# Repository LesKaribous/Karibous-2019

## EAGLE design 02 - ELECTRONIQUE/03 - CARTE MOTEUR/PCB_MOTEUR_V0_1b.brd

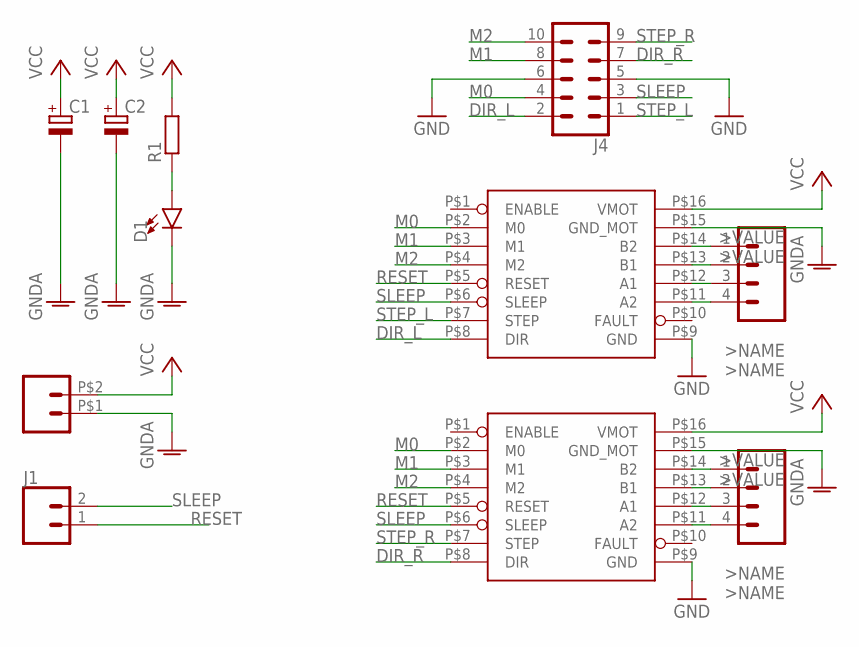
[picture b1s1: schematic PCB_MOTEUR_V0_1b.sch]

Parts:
C1, C2: CPOL-EUE3.5-8; E3,5-8
D1: LED3MM; LED_3MM
J1: CONN_02; 1X02
J2: CONN_027A-C; NSK396-2C
J3, J5: CONN_04POLAR; MOLEX-1X4
J4: CONN_05X2SHD; 2X5-SHROUDED
R1: R-EU_0207/2V; 0207/2V
U$1, U$2: DRV8825; DRIVER_CARRIER_POLOLU_16

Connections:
DIR_L: J4.2, U$1.P$8 (DIR)
DIR_R: J4.7, U$2.P$8 (DIR)
GND: J4.5, J4.6, U$1.P$9 (GND), U$2.P$9 (GND)
GNDA: C1.-, C2.-, D1.K (C), J2.P$1 (1), U$1.P$15 (GND_MOT), U$2.P$15 (GND_MOT)
M0: J4.4, U$1.P$2 (M0), U$2.P$2 (M0)
M1: J4.8, U$1.P$3 (M1), U$2.P$3 (M1)
M2: J4.10, U$1.P$4 (M2), U$2.P$4 (M2)
unnamed: J3.1, U$1.P$14 (B2)
unnamed: J3.2, U$1.P$13 (B1)
unnamed: J3.3, U$1.P$12 (A1)
unnamed: J3.4, U$1.P$11 (A2)
unnamed: D1.A, R1.1
unnamed: J5.1, U$2.P$14 (B2)
unnamed: J5.2, U$2.P$13 (B1)
unnamed: J5.3, U$2.P$12 (A1)
unnamed: J5.4, U$2.P$11 (A2)
RESET: J1.1, U$1.P$5 (RESET), U$2.P$5 (RESET)
SLEEP: J1.2, J4.3, U$1.P$6 (SLEEP), U$2.P$6 (SLEEP)
STEP_L: J4.1, U$1.P$7 (STEP)
STEP_R: J4.9, U$2.P$7 (STEP)
VCC: C1.+, C2.+, J2.P$2 (2), R1.2, U$1.P$16 (VMOT), U$2.P$16 (VMOT)

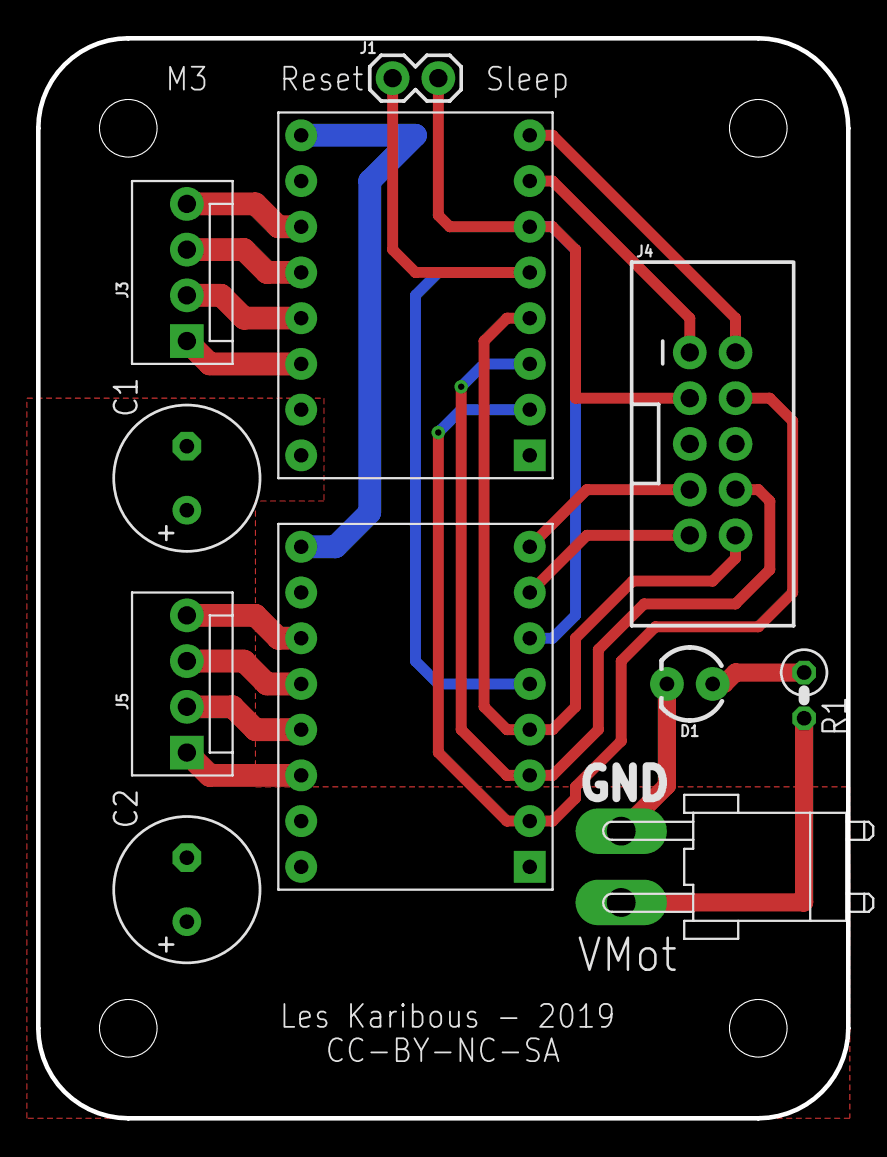
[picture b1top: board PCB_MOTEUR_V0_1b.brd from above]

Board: 2 copper layers, 45.0 x 60.0 mm, 11 parts (0 on the bottom side), 21 nets.

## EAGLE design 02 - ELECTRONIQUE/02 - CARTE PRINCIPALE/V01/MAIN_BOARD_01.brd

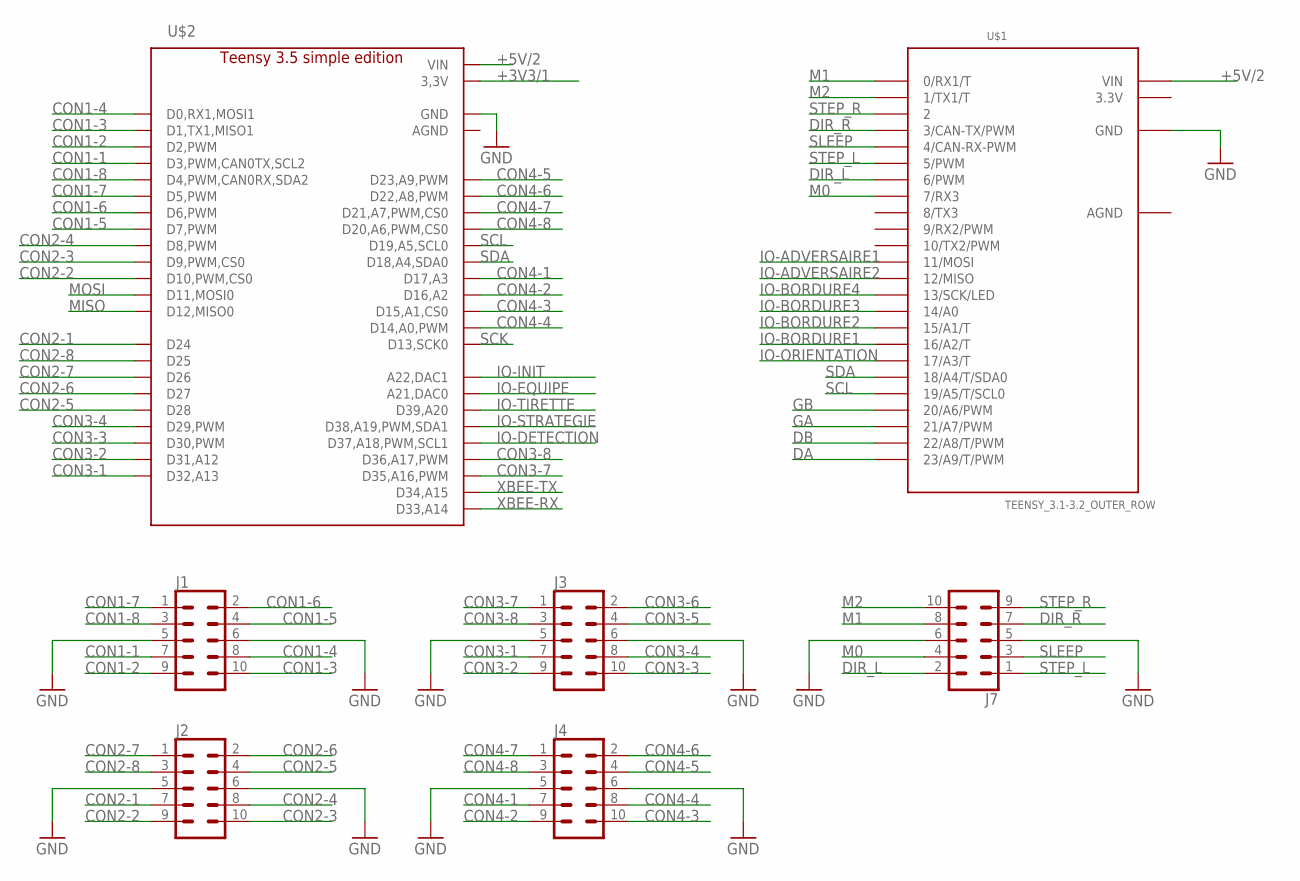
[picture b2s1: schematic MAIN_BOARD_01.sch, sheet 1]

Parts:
J1, J2, J3, J4, J7: CONN_05X2SHD; 2X5-SHROUDED
U$1: TEENSY_3.1-3.2_OUTER_ROW; TEENSY_3.0-3.2&LC_OUTER_ROW
U$2: TEENSY_3.5; TEENSY_3.5_LIGHT

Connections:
3.3V: U$1.3.3V
+3V3/1: U$2.P$15 (3,3V), U$2.P$46 (3,3V); also elsewhere on the board
+5V/2: U$1.V_IN (VIN), U$2.P$48 (VIN); also elsewhere on the board
AGND: U$1.AGND
CON1-1: J1.7, U$2.P$5 (D3,PWM,CAN0TX,SCL2)
CON1-2: J1.9, U$2.P$4 (D2,PWM)
CON1-3: J1.10, U$2.P$3 (D1,TX1,MISO1)
CON1-4: J1.8, U$2.P$2 (D0,RX1,MOSI1)
CON1-5: J1.4, U$2.P$9 (D7,PWM)
CON1-6: J1.2, U$2.P$8 (D6,PWM)
CON1-7: J1.1, U$2.P$7 (D5,PWM)
CON1-8: J1.3, U$2.P$6 (D4,PWM,CAN0RX,SDA2)
CON2-1: J2.7, U$2.P$16 (D24)
CON2-2: J2.9, U$2.P$12 (D10,PWM,CS0)
CON2-3: J2.10, U$2.P$11 (D9,PWM,CS0)
CON2-4: J2.8, U$2.P$10 (D8,PWM)
CON2-5: J2.4, U$2.P$20 (D28)
CON2-6: J2.2, U$2.P$19 (D27)
CON2-7: J2.1, U$2.P$18 (D26)
CON2-8: J2.3, U$2.P$17 (D25)
CON3-1: J3.7, U$2.P$24 (D32,A13)
CON3-2: J3.9, U$2.P$23 (D31,A12)
CON3-3: J3.10, U$2.P$22 (D30,PWM)
CON3-4: J3.8, U$2.P$21 (D29,PWM)
CON3-5: J3.4
CON3-6: J3.2
CON3-7: J3.1, U$2.P$27 (D35,A16,PWM)
CON3-8: J3.3, U$2.P$28 (D36,A17,PWM)
CON4-1: J4.7, U$2.P$39 (D17,A3)
CON4-2: J4.9, U$2.P$38 (D16,A2)
CON4-3: J4.10, U$2.P$37 (D15,A1,CS0)
CON4-4: J4.8, U$2.P$36 (D14,A0,PWM)
CON4-5: J4.4, U$2.P$45 (D23,A9,PWM)
CON4-6: J4.2, U$2.P$44 (D22,A8,PWM)
CON4-7: J4.1, U$2.P$43 (D21,A7,PWM,CS0)
CON4-8: J4.3, U$2.P$42 (D20,A6,PWM,CS0)
DA: U$1.23/A9 (23/A9/T/PWM); also elsewhere on the board
DB: U$1.22/A8 (22/A8/T/PWM); also elsewhere on the board
DIR_L: J7.2, U$1.6 (6/PWM)
DIR_R: J7.7, U$1.3 (3/CAN-TX/PWM)
GA: U$1.21/A7 (21/A7/PWM); also elsewhere on the board
GB: U$1.20/A6 (20/A6/PWM); also elsewhere on the board
GND: J1.5, J1.6, J2.5, J2.6, J3.5, J3.6, J4.5, J4.6, J7.5, J7.6, U$1.GND, U$2.GND, U$2.P$34 (GND); also elsewhere on the board
IO-ADVERSAIRE1: U$1.11 (11/MOSI); also elsewhere on the board
IO-ADVERSAIRE2: U$1.12 (12/MISO); also elsewhere on the board
IO-BORDURE1: U$1.16/A2 (16/A2/T); also elsewhere on the board
IO-BORDURE2: U$1.15/A1 (15/A1/T); also elsewhere on the board
IO-BORDURE3: U$1.14/A0; also elsewhere on the board
IO-BORDURE4: U$1.13 (13/SCK/LED); also elsewhere on the board
IO-DETECTION: U$2.P$29 (D37,A18,PWM,SCL1); also elsewhere on the board
IO-EQUIPE: U$2.P$32 (A21,DAC0); also elsewhere on the board
IO-INIT: U$2.P$33 (A22,DAC1); also elsewhere on the board
IO-ORIENTATION: U$1.17/A3 (17/A3/T); also elsewhere on the board
IO-STRATEGIE: U$2.P$30 (D38,A19,PWM,SDA1); also elsewhere on the board
IO-TIRETTE: U$2.P$31 (D39,A20); also elsewhere on the board
M0: J7.4, U$1.7 (7/RX3)
M1: J7.8, U$1.0 (0/RX1/T)
M2: J7.10, U$1.1 (1/TX1/T)
MISO: U$2.P$14 (D12,MISO0); also elsewhere on the board
MOSI: U$2.P$13 (D11,MOSI0); also elsewhere on the board
SCK: U$2.P$35 (D13,SCK0); also elsewhere on the board
SCL: U$1.19/A5 (19/A5/T/SCL0), U$2.P$41 (D19,A5,SCL0); also elsewhere on the board
SDA: U$1.18/A4 (18/A4/T/SDA0), U$2.P$40 (D18,A4,SDA0); also elsewhere on the board
SLEEP: J7.3, U$1.4 (4/CAN-RX-PWM)
STEP_L: J7.1, U$1.5 (5/PWM)
STEP_R: J7.9, U$1.2
XBEE-RX: U$2.P$25 (D33,A14); also elsewhere on the board
XBEE-TX: U$2.P$26 (D34,A15); also elsewhere on the board

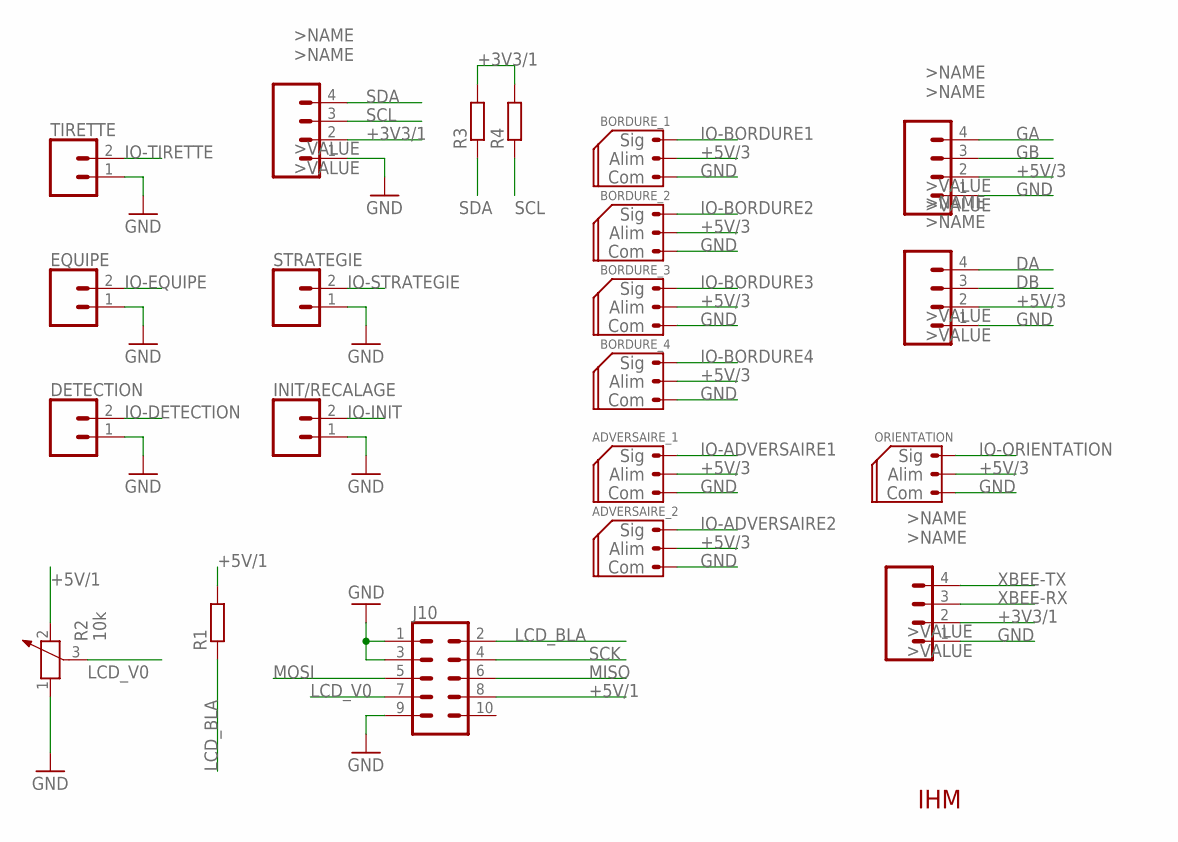
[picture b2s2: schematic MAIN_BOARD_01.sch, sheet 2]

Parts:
ADVERSAIRE_1, ADVERSAIRE_2: CONN_03_SERVO; MOLEX-1X3
BORDURE_1, BORDURE_2, BORDURE_3, BORDURE_4: CONN_03_SERVO; MOLEX-1X3
COM-I2C: CONN_04POLAR; MOLEX-1X4
COM-XBEE: CONN_04POLAR; MOLEX-1X4
DETECTION: CONN_02POLAR; MOLEX-1X2
ENC_DROIT: CONN_04POLAR; MOLEX-1X4
ENC_GAUCHE: CONN_04POLAR; MOLEX-1X4
EQUIPE: CONN_02POLAR; MOLEX-1X2
INIT/RECALAGE: CONN_02POLAR; MOLEX-1X2
J10: CONN_05X2SHD; 2X5-SHROUDED
ORIENTATION: CONN_03_SERVO; MOLEX-1X3
R1, R3, R4: R-EU_R1206; R1206
R2: 10k; PT-10
STRATEGIE: CONN_02POLAR; MOLEX-1X2
TIRETTE: CONN_02POLAR; MOLEX-1X2

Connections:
+3V3/1: COM-I2C.2, COM-XBEE.2, R3.2, R4.2; also elsewhere on the board
+5V/1: J10.8, R1.2, R2.2; also elsewhere on the board
+5V/3: ADVERSAIRE_1.2, ADVERSAIRE_2.2, BORDURE_1.2, BORDURE_2.2, BORDURE_3.2, BORDURE_4.2, ENC_DROIT.2, ENC_GAUCHE.2, ORIENTATION.2; also elsewhere on the board
DA: ENC_DROIT.4; also elsewhere on the board
DB: ENC_DROIT.3; also elsewhere on the board
GA: ENC_GAUCHE.4; also elsewhere on the board
GB: ENC_GAUCHE.3; also elsewhere on the board
GND: ADVERSAIRE_1.1, ADVERSAIRE_2.1, BORDURE_1.1, BORDURE_2.1, BORDURE_3.1, BORDURE_4.1, COM-I2C.1, COM-XBEE.1, DETECTION.1, ENC_DROIT.1, ENC_GAUCHE.1, EQUIPE.1, INIT/RECALAGE.1, J10.1, J10.3, J10.9, ORIENTATION.1, R2.1, STRATEGIE.1, TIRETTE.1; also elsewhere on the board
IO-ADVERSAIRE1: ADVERSAIRE_1.3; also elsewhere on the board
IO-ADVERSAIRE2: ADVERSAIRE_2.3; also elsewhere on the board
IO-BORDURE1: BORDURE_1.3; also elsewhere on the board
IO-BORDURE2: BORDURE_2.3; also elsewhere on the board
IO-BORDURE3: BORDURE_3.3; also elsewhere on the board
IO-BORDURE4: BORDURE_4.3; also elsewhere on the board
IO-DETECTION: DETECTION.2; also elsewhere on the board
IO-EQUIPE: EQUIPE.2; also elsewhere on the board
IO-INIT: INIT/RECALAGE.2; also elsewhere on the board
IO-ORIENTATION: ORIENTATION.3; also elsewhere on the board
IO-STRATEGIE: STRATEGIE.2; also elsewhere on the board
IO-TIRETTE: TIRETTE.2; also elsewhere on the board
LCD_BLA: J10.2, R1.1
LCD_V0: J10.7, R2.3
MISO: J10.6; also elsewhere on the board
MOSI: J10.5; also elsewhere on the board
SCK: J10.4; also elsewhere on the board
SCL: COM-I2C.3, R4.1; also elsewhere on the board
SDA: COM-I2C.4, R3.1; also elsewhere on the board
XBEE-RX: COM-XBEE.3; also elsewhere on the board
XBEE-TX: COM-XBEE.4; also elsewhere on the board

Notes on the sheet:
IHM

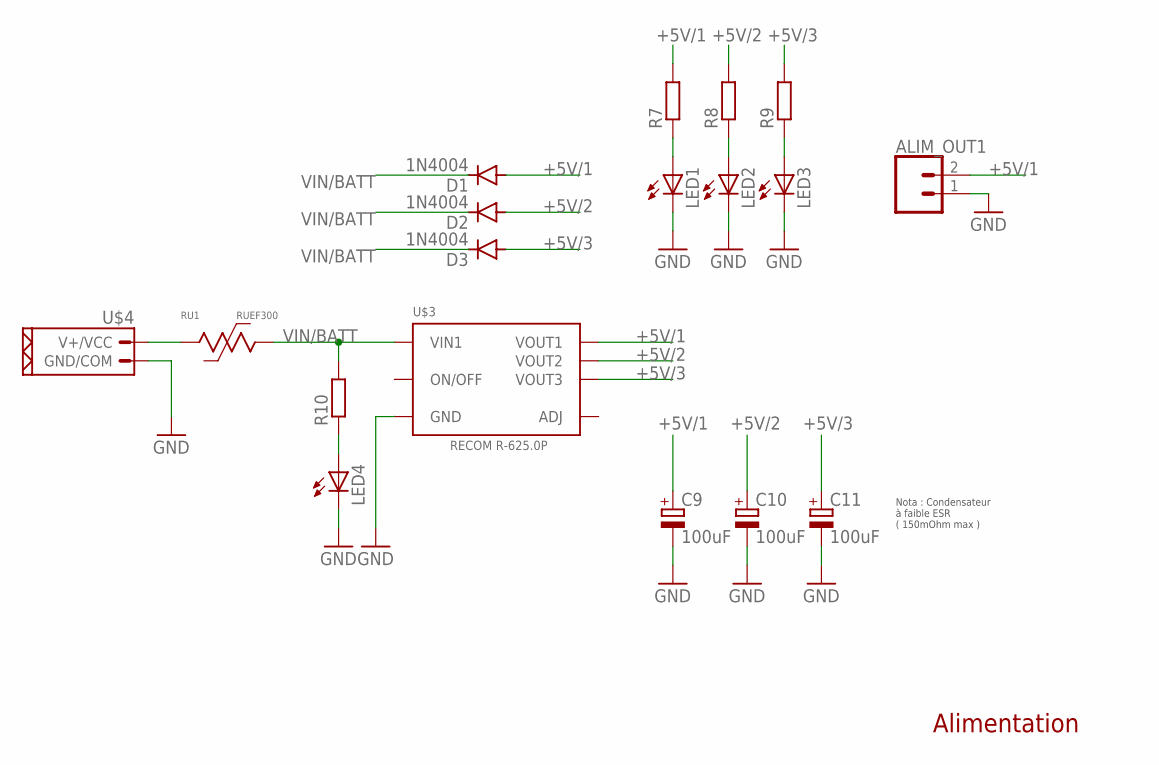
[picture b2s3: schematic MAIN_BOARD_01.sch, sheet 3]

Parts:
ALIM_OUT1: CONN_02POLAR; MOLEX-1X2
C9, C10, C11: 100uF; E5-10,5
D1, D2, D3: 1N4004; DO41-10
LED1, LED2, LED3, LED4: LED_E; LED_1206
R7, R8, R9, R10: R-EU_R1206; R1206
RU1: RUEF300
U$3: R-625.0P; R-6XXXP
U$4: CONN_02_PUI; NSK396-2C

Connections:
+5V/1: ALIM_OUT1.2, C9.+, D1.A, R7.2, U$3.P$9 (VOUT1); also elsewhere on the board
+5V/2: C10.+, D2.A, R8.2, U$3.P$10 (VOUT2); also elsewhere on the board
+5V/3: C11.+, D3.A, R9.2, U$3.P$11 (VOUT3); also elsewhere on the board
ADJ: U$3.P$12 (ADJ)
GND: ALIM_OUT1.1, C9.-, C10.-, C11.-, LED1.C, LED2.C, LED3.C, LED4.C, U$3.P$5 (GND), U$3.P$6 (GND), U$3.P$7 (GND), U$3.P$8 (GND), U$4.P$1 (GND/COM); also elsewhere on the board
unnamed: LED1.A, R7.1
unnamed: LED4.A, R10.1
unnamed: RU1.P$1, U$4.P$2 (V+/VCC)
unnamed: LED2.A, R8.1
unnamed: LED3.A, R9.1
VIN/BATT: D1.C, D2.C, D3.C, R10.2, RU1.P$2, U$3.P$2 (VIN1), U$3.P$3 (VIN1), U$3.P$4 (VIN1)

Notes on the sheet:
Nota : Condensateur à faible ESR ( 150mOhm max )
Alimentation

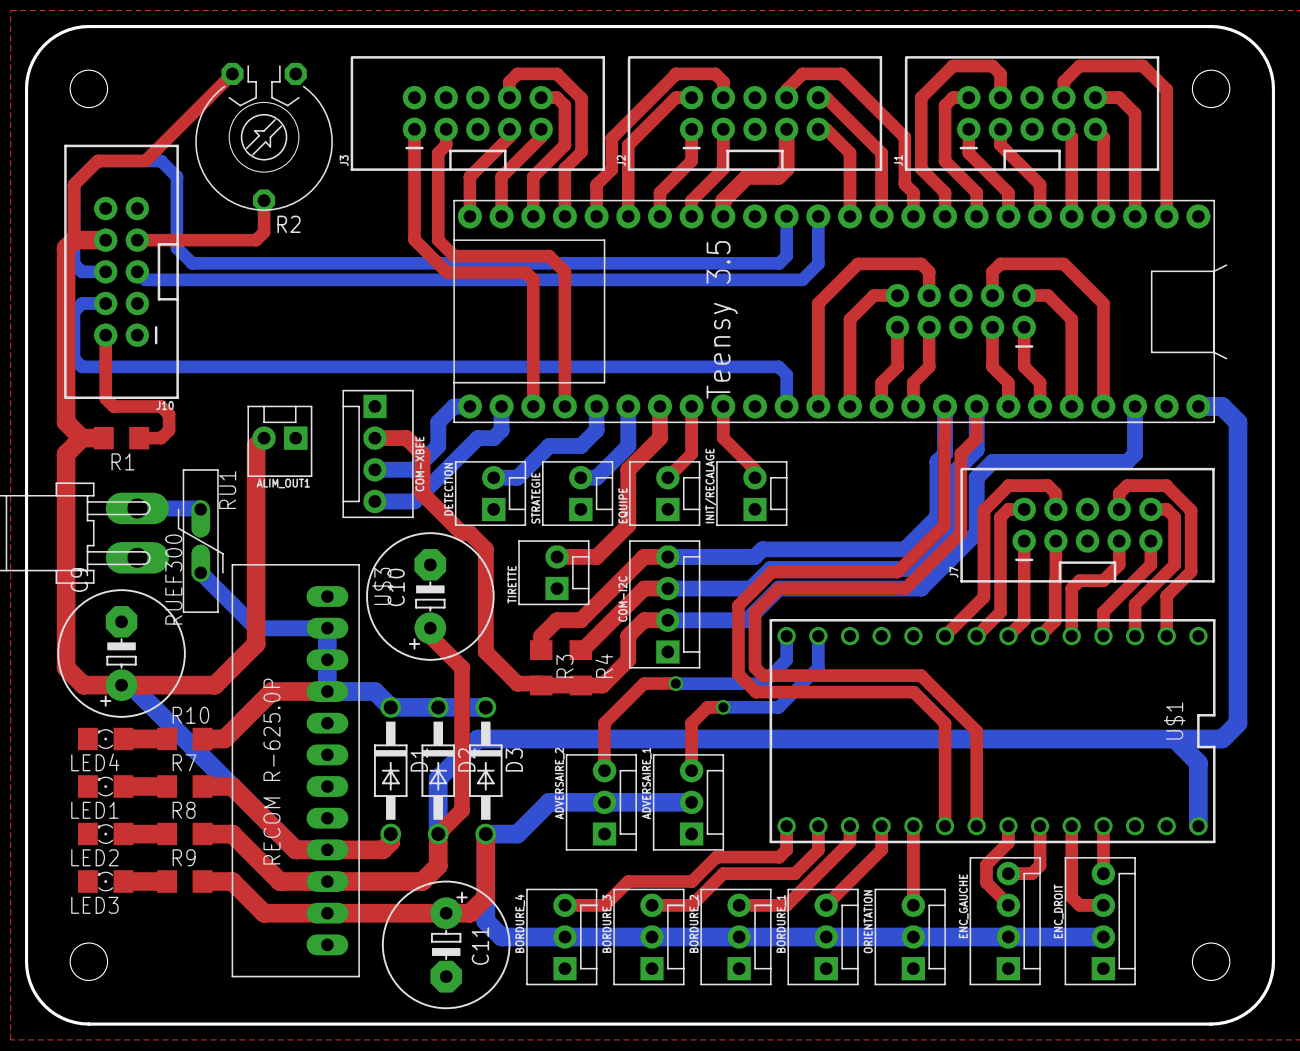
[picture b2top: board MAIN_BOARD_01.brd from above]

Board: 2 copper layers, 100.0 x 80.0 mm, 46 parts (1 on the bottom side), 74 nets.

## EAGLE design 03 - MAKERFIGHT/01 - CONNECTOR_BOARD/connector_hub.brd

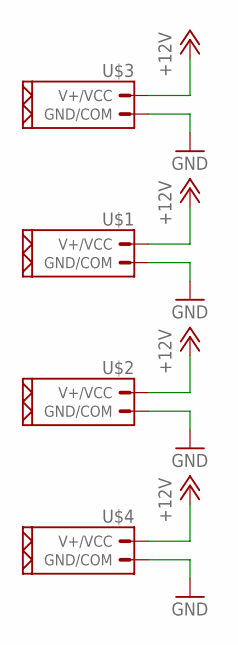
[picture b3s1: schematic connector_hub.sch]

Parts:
U$1, U$2, U$3, U$4: CONN_02_PUIXT60; XT60

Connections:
+12V: U$1.P$1 (V+/VCC), U$2.P$1 (V+/VCC), U$3.P$1 (V+/VCC), U$4.P$1 (V+/VCC)
GND: U$1.P$2 (GND/COM), U$2.P$2 (GND/COM), U$3.P$2 (GND/COM), U$4.P$2 (GND/COM)

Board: 2 copper layers, 4 parts (0 on the bottom side), 2 nets, no tracks yet.

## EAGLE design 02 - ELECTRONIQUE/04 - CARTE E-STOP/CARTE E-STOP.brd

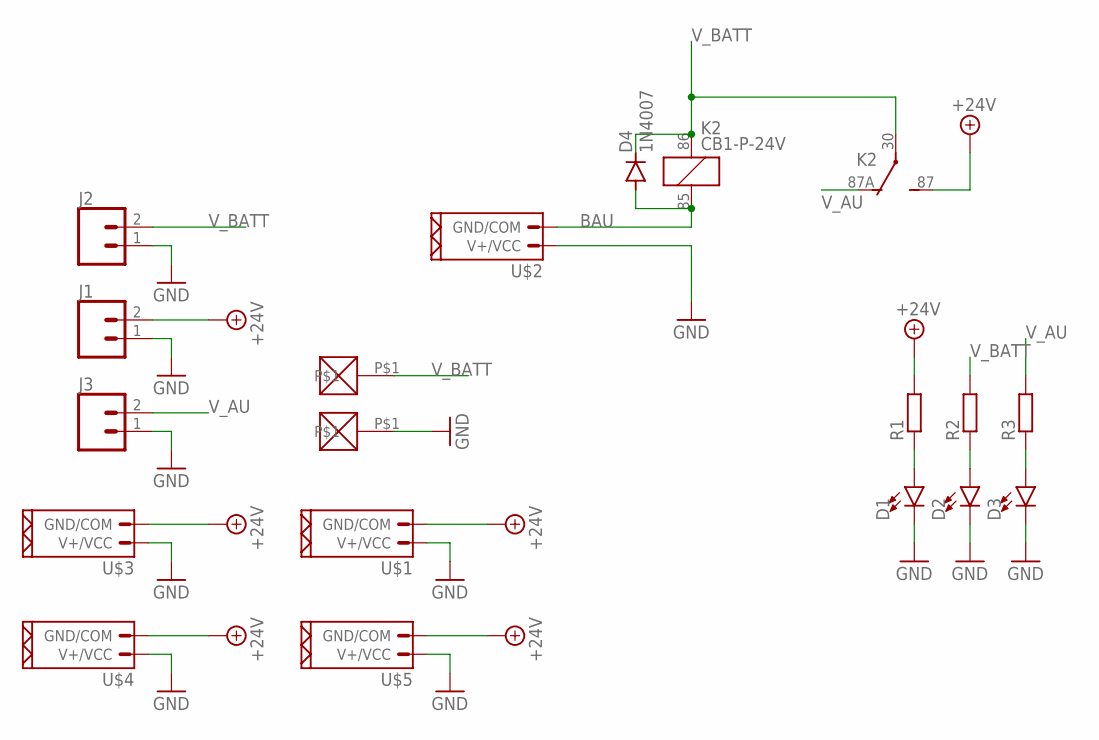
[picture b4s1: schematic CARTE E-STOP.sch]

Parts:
D1, D2, D3: LED3MM; LED_3MM
D4: 1N4007; DO41-10
GND_BATT: BAT_WIRE_SOLD; LARGE_PAD_BATT
J1, J2, J3: CONN_02POLAR; MOLEX-1X2
K2: CB1-P-24V; CB1
R1, R2, R3: R-EU_0207/2V; 0207/2V
U$1, U$2, U$3, U$4, U$5: CONN_02_PUI; NSK396-2C
V+BATT: BAT_WIRE_SOLD; LARGE_PAD_BATT

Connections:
+24V: J1.2, K2.87 (S), R1.2, U$1.P$1 (GND/COM), U$3.P$1 (GND/COM), U$4.P$1 (GND/COM), U$5.P$1 (GND/COM)
BAU: D4.A, K2.85 (2), U$2.P$1 (GND/COM)
GND: D1.K (C), D2.K (C), D3.K (C), GND_BATT.P$1, J1.1, J2.1, J3.1, U$1.P$2 (V+/VCC), U$2.P$2 (V+/VCC), U$3.P$2 (V+/VCC), U$4.P$2 (V+/VCC), U$5.P$2 (V+/VCC)
unnamed: D1.A, R1.1
unnamed: D2.A, R2.1
unnamed: D3.A, R3.1
V_AU: J3.2, K2.87A (O), R3.2
V_BATT: D4.C, J2.2, K2.30, K2.86 (1), R2.2, V+BATT.P$1

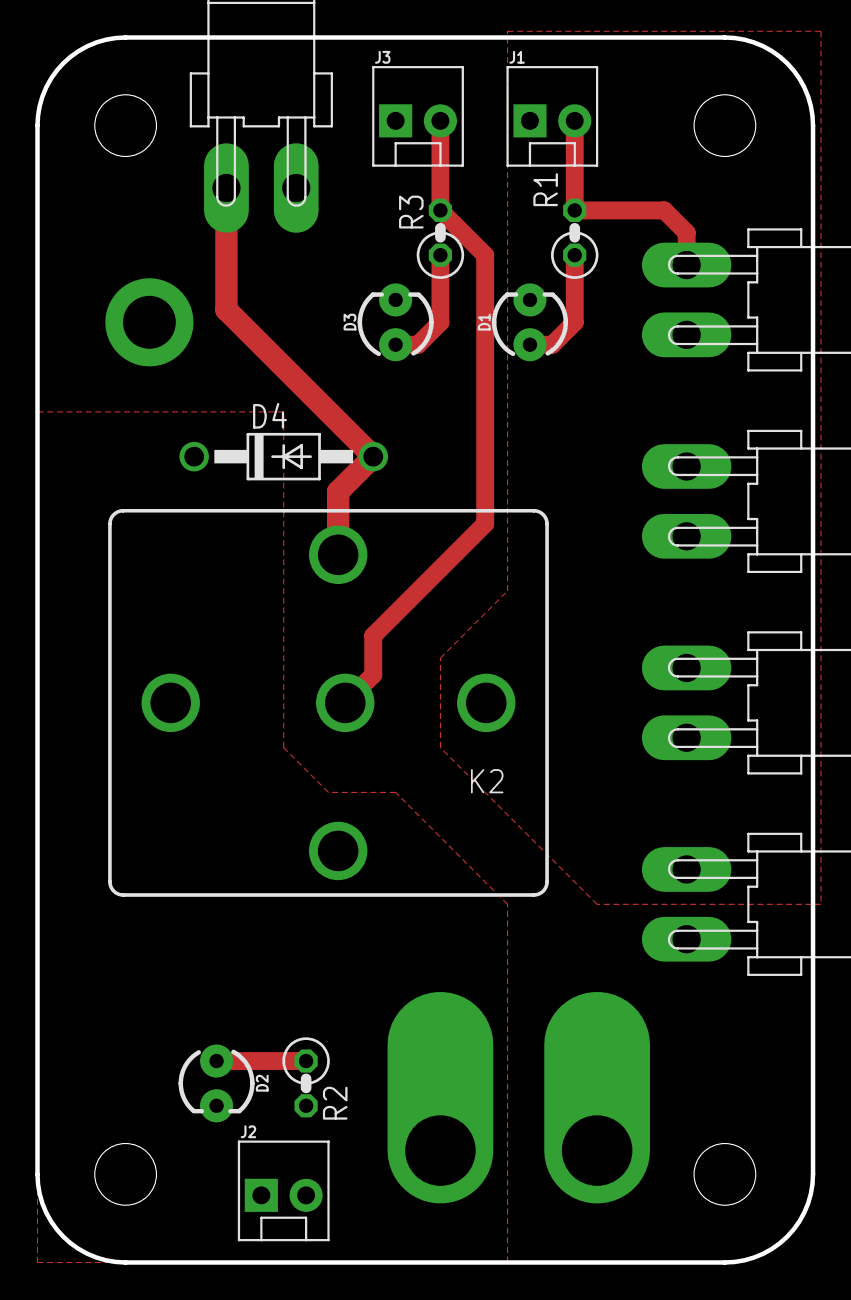
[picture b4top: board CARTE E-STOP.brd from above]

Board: 2 copper layers, 44.0 x 69.5 mm, 18 parts (0 on the bottom side), 8 nets.

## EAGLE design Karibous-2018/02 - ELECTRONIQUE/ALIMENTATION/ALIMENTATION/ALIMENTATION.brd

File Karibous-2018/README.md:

# Karibous-2018
Les Karibous - Coupe de France de robotique 2018

Fichiers de l'electronqiue et de la partie programmation du robot 2018 de l'équipe des Karibous.
Pour la documentation et les fichiers mécaniques, veuillez vous reporter à notre site web : https://sites.google.com/view/leskaribous/la-coupe-de-robotique/robot-2018

### Licence :
L'integralité du contenu est utlisable sous licence CC-BY-NC-SA

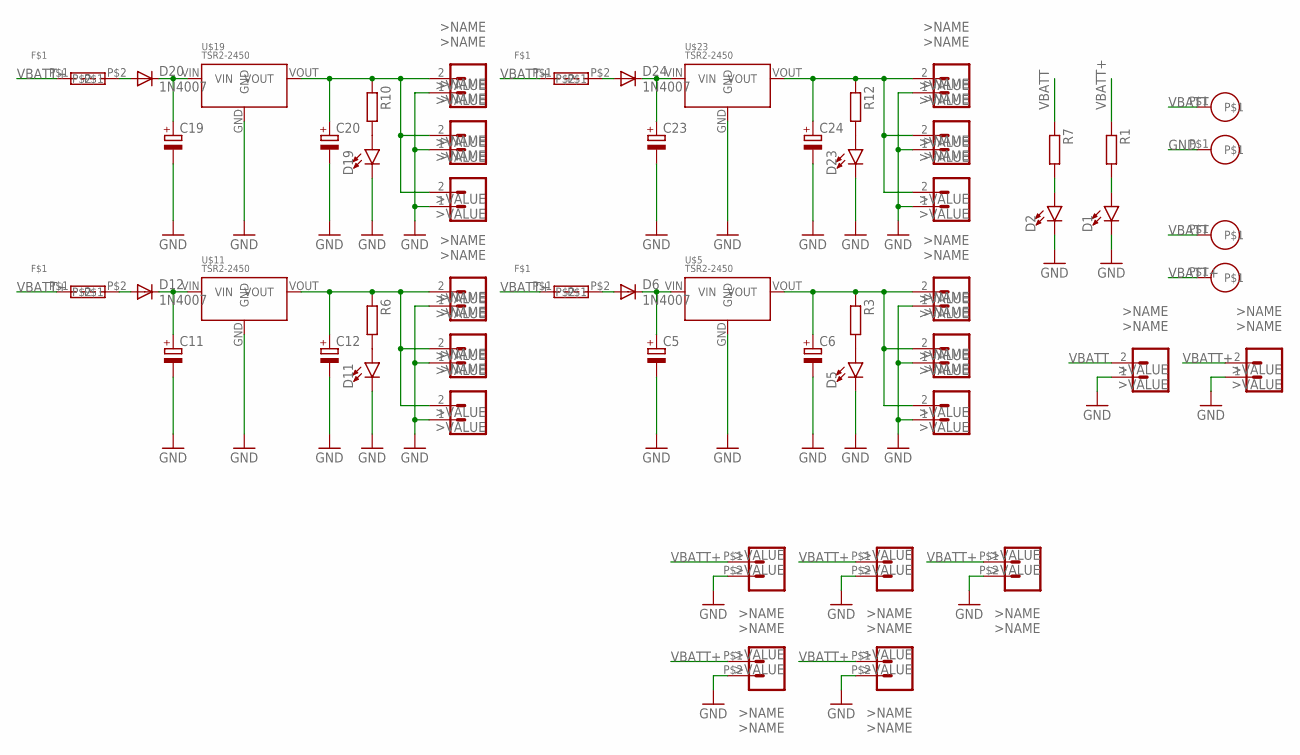
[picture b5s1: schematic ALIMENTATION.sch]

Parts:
C5, C6, C11, C12, C19, C20, C23, C24: CPOL-EUE2-5; E2-5
D1, D2, D5, D11, D19, D23: LED3MM; LED_3MM
D6, D12, D20, D24: 1N4007; DO41-10
J1, J2, J7, J8, J9, J16, J17, J18, J28, J29, J30, J34, J35, J36: CONN_02POLAR; MOLEX-1X2
J3, J10, J11, J12, J13: CONN_027A-C; NSK396-2C
R1, R3, R6, R7, R10, R12: R-EU_0204/2V; 0204V
U$1, U$2, U$13, U$14: BATTERY_PAD
U$5, U$11, U$19, U$23: TSR2-2450
U$6, U$12, U$20, U$24: RUEF_POLY; RUEF185

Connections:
GND: C5.-, C6.-, C11.-, C12.-, C19.-, C20.-, C23.-, C24.-, D1.K (C), D2.K (C), D5.K (C), D11.K (C), D19.K (C), D23.K (C), J1.1, J2.1, J3.P$2 (2), J7.1, J8.1, J9.1, J10.P$2 (2), J11.P$2 (2), J12.P$2 (2), J13.P$2 (2), J16.1, J17.1, J18.1, J28.1, J29.1, J30.1, J34.1, J35.1, J36.1, U$2.P$1, U$5.GND, U$11.GND, U$19.GND, U$23.GND
unnamed: D1.A, R1.2
unnamed: D2.A, R7.2
unnamed: C6.+, J7.2, J8.2, J9.2, R3.1, U$5.VOUT
unnamed: D5.A, R3.2
unnamed: C5.+, D6.C, U$5.VIN
unnamed: D6.A, U$6.P$2
unnamed: C12.+, J16.2, J17.2, J18.2, R6.1, U$11.VOUT
unnamed: D11.A, R6.2
unnamed: C11.+, D12.C, U$11.VIN
unnamed: D12.A, U$12.P$2
unnamed: C20.+, J28.2, J29.2, J30.2, R10.1, U$19.VOUT
unnamed: D19.A, R10.2
unnamed: C19.+, D20.C, U$19.VIN
unnamed: D20.A, U$20.P$2
unnamed: C24.+, J34.2, J35.2, J36.2, R12.1, U$23.VOUT
unnamed: D23.A, R12.2
unnamed: C23.+, D24.C, U$23.VIN
unnamed: D24.A, U$24.P$2
VBATT: J1.2, R7.1, U$1.P$1, U$13.P$1
VBATT+: J2.2, J3.P$1 (1), J10.P$1 (1), J11.P$1 (1), J12.P$1 (1), J13.P$1 (1), R1.1, U$6.P$1, U$12.P$1, U$14.P$1, U$20.P$1, U$24.P$1

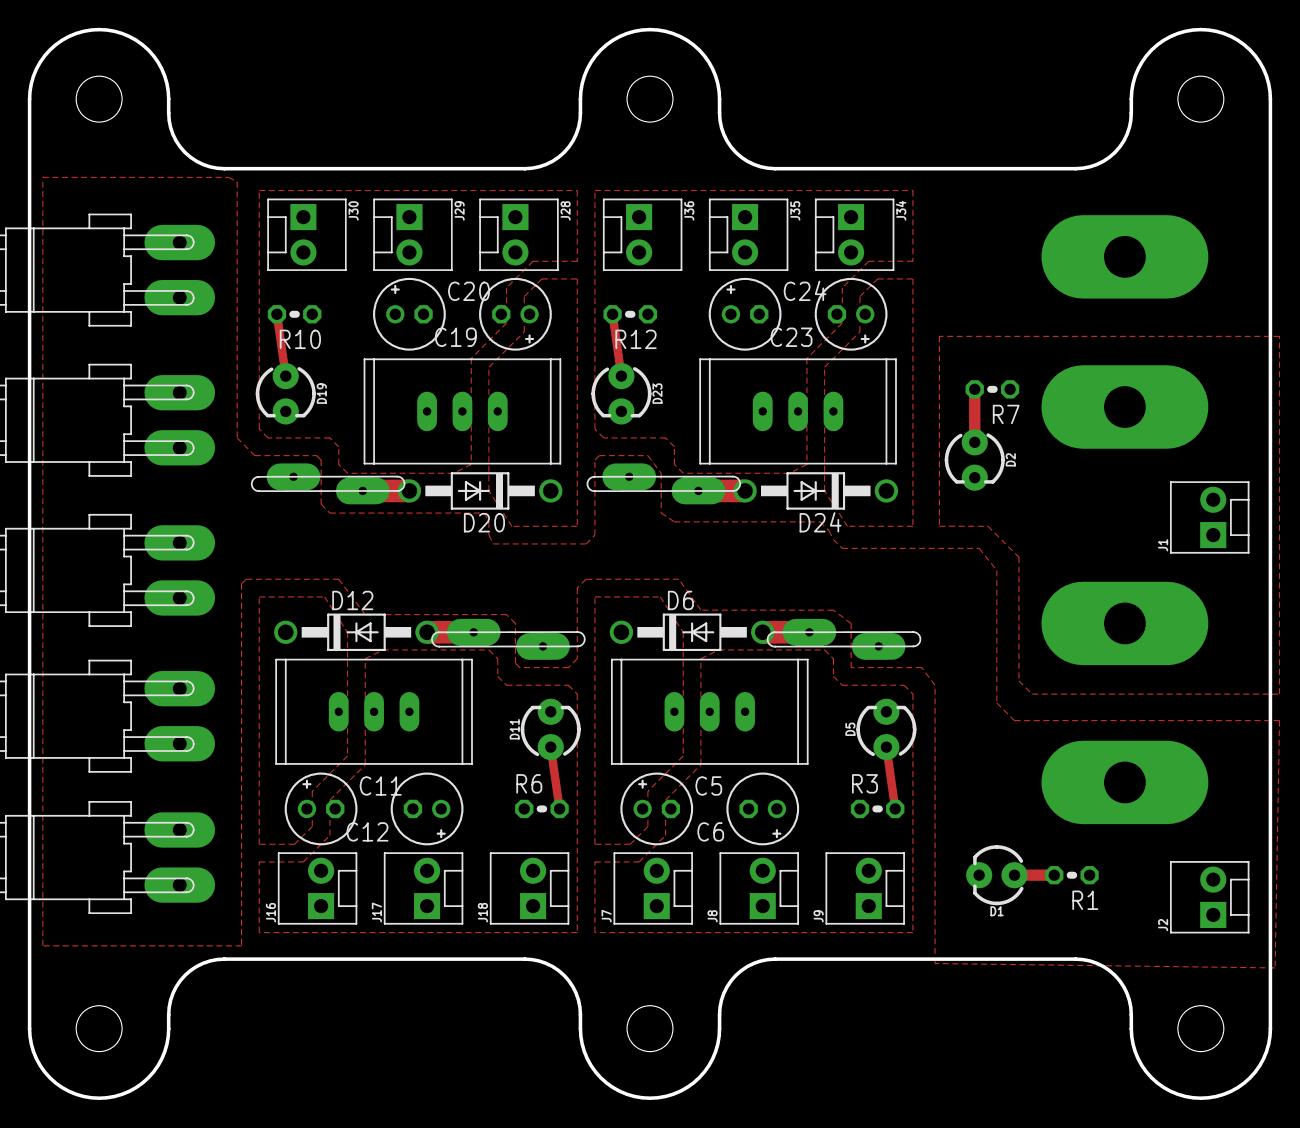
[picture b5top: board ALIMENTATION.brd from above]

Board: 2 copper layers, 89.2 x 76.8 mm, 55 parts (0 on the bottom side), 21 nets.

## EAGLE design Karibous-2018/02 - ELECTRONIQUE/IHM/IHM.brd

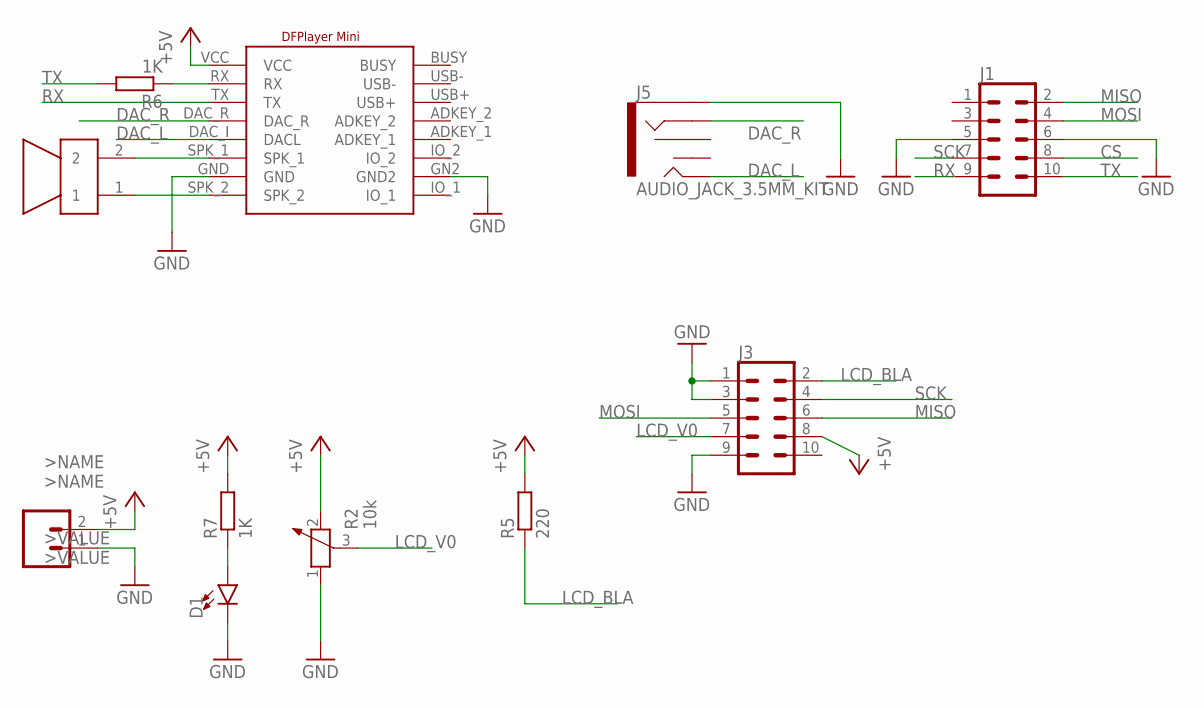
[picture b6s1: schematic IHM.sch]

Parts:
D1: LED3MM; LED_3MM
J1, J3: CONN_05X2SHD; 2X5-SHROUDED
J2: CONN_02POLAR; MOLEX-1X2
J5: AUDIO_JACK_3.5MM_KIT; AUDIO-JACK-KIT
R2: 10k; PT-10
R5: 220; 0207/10
R6, R7: 1K; 0207/10
U$1: AST-01508MR-WT-R
U$2: DFPLAYER_MINI

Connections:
+5V: J2.2, J3.8, R2.2, R5.2, R7.2, U$2.VCC
CS: J1.8
DAC_L: J5.TIP, U$2.DAC_I (DACL)
DAC_R: J5.RING, U$2.DAC_R
GND: D1.K (C), J1.5, J1.6, J2.1, J3.1, J3.3, J3.9, J5.SLEEVE, R2.1, U$2.GN2 (GND2), U$2.GND
LCD_BLA: J3.2, R5.1
LCD_V0: J3.7, R2.3
MISO: J1.2, J3.6
MOSI: J1.4, J3.5
unnamed: D1.A, R7.1
unnamed: U$1.2, U$2.SPK_1
unnamed: U$1.1, U$2.SPK_2
unnamed: R6.1, U$2.RX
RX: J1.9, U$2.TX
SCK: J1.7, J3.4
TX: J1.10, R6.2

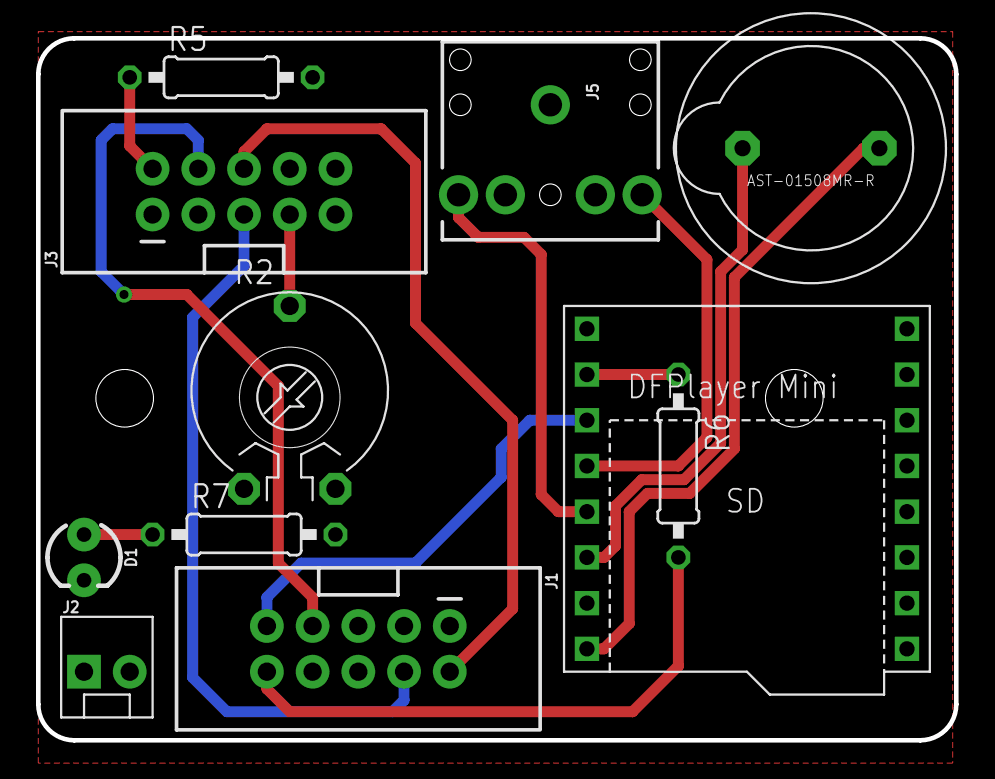
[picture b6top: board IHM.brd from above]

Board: 2 copper layers, 51.0 x 39.0 mm, 11 parts (0 on the bottom side), 15 nets.

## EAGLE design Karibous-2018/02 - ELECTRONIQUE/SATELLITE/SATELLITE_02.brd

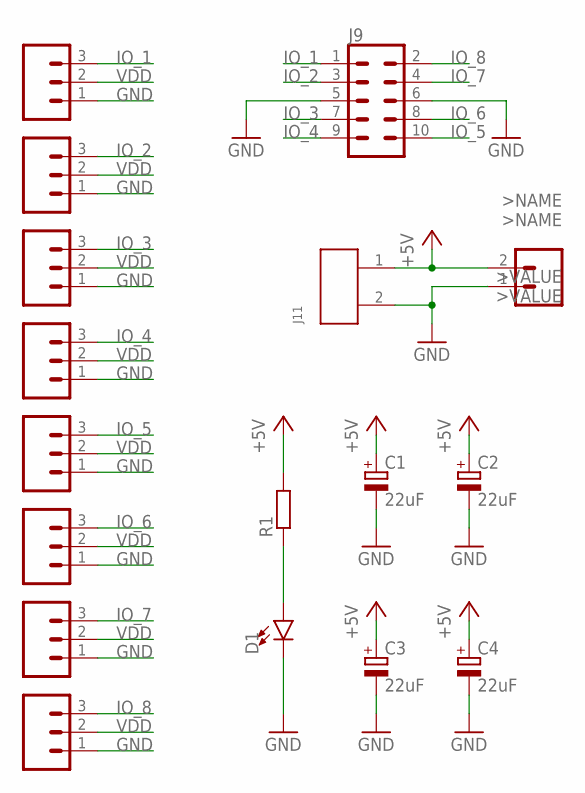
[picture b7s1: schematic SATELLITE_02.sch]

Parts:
C1, C2, C3, C4: 22uF; E2-5
D1: LED3MM; LED_3MM
J1, J2, J3, J4, J5, J6, J7, J8: CONN_03; 1X03
J9: CONN_05X2SHD; 2X5-SHROUDED
J10: CONN_02POLAR; MOLEX-1X2
J11: 645002114822
R1: R-EU_0204/7; 0204/7

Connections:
GND: C1.-, C2.-, C3.-, C4.-, D1.K (C), J1.1, J2.1, J3.1, J4.1, J5.1, J6.1, J7.1, J8.1, J9.5, J9.6, J10.1, J11.2
IO_1: J7.3, J9.1
IO_2: J8.3, J9.3
IO_3: J1.3, J9.7
IO_4: J2.3, J9.9
IO_5: J3.3, J9.10
IO_6: J4.3, J9.8
IO_7: J5.3, J9.4
IO_8: J6.3, J9.2
unnamed: D1.A, R1.1
VDD: C1.+, C2.+, C3.+, C4.+, J1.2, J2.2, J3.2, J4.2, J5.2, J6.2, J7.2, J8.2, J10.2, J11.1, R1.2

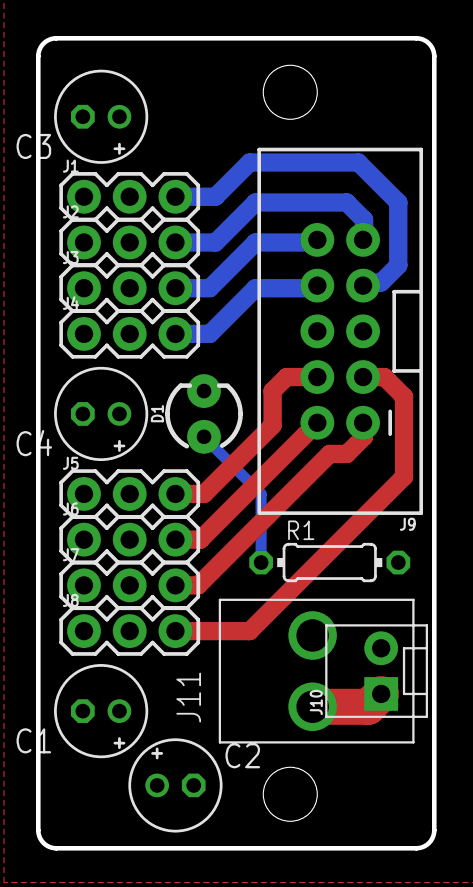
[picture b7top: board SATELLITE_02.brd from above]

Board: 2 copper layers, 22.0 x 45.0 mm, 17 parts (0 on the bottom side), 11 nets.

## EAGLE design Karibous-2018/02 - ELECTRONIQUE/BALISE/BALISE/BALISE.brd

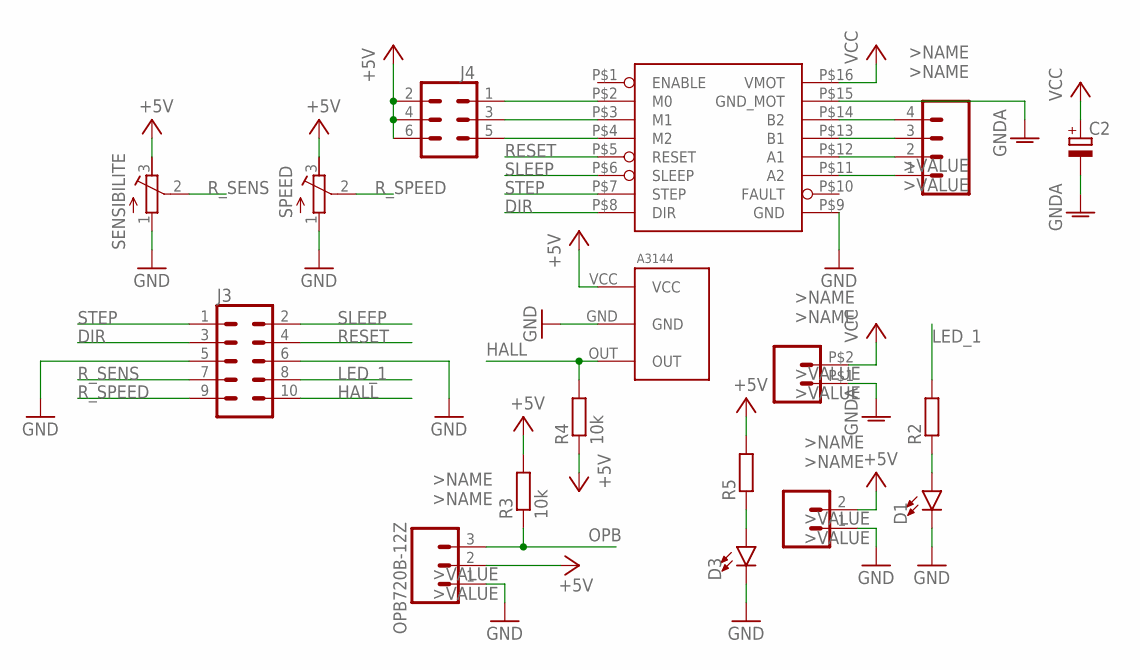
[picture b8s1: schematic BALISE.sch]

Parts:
A3144: A3144_HALL_SENSOR; A3144_HORIZONTAL
C2: CPOL-EUE3.5-8; E3,5-8
D1, D3: LED5MM; LED_5MM
J1: CONN_04POLAR; MOLEX-1X4
J2: CONN_02POLAR; MOLEX-1X2
J3: CONN_05X2SHD; 2X5-SHROUDED
J4: CONN_03X22X3_SILK_MALE_PTH; 2X3
J5: CONN_027A-C; NSK396-2C
OPB720B-12Z: CONN_03POLAR; MOLEX-1X3
R2, R5: R-EU_0207/10; 0207/10
R3, R4: 10k; 0207/10
SENSIBILITE: R-TRIMM3339P; RTRIM3339P
SPEED: R-TRIMM3339P; RTRIM3339P
U$1: DRV8825; DRIVER_CARRIER_POLOLU_16

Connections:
+5V: A3144.VCC, J2.2, J4.2, J4.4, J4.6, OPB720B-12Z.2, R3.2, R4.1, R5.2, SENSIBILITE.3 (E), SPEED.3 (E)
DIR: J3.3, U$1.P$8 (DIR)
GND: A3144.GND, D1.K (C), D3.K (C), J2.1, J3.5, J3.6, OPB720B-12Z.1, SENSIBILITE.1 (A), SPEED.1 (A), U$1.P$9 (GND)
GNDA: C2.-, J5.P$1 (1), U$1.P$15 (GND_MOT)
HALL: A3144.OUT, J3.10, R4.2
LED_1: J3.8, R2.2
unnamed: D1.A, R2.1
unnamed: J1.4, U$1.P$14 (B2)
unnamed: J1.3, U$1.P$13 (B1)
unnamed: J4.1, U$1.P$2 (M0)
unnamed: D3.A, R5.1
unnamed: J1.2, U$1.P$12 (A1)
unnamed: J1.1, U$1.P$11 (A2)
unnamed: J4.3, U$1.P$3 (M1)
unnamed: J4.5, U$1.P$4 (M2)
OPB: OPB720B-12Z.3, R3.1
RESET: J3.4, U$1.P$5 (RESET)
R_SENS: J3.7, SENSIBILITE.2 (S)
R_SPEED: J3.9, SPEED.2 (S)
SLEEP: J3.2, U$1.P$6 (SLEEP)
STEP: J3.1, U$1.P$7 (STEP)
VCC: C2.+, J5.P$2 (2), U$1.P$16 (VMOT)

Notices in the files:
parts and their libraries:
SparkFun-Connectors: Licensing: Creative Commons ShareAlike 4.0 International - https://creativecommons.org/licenses/by-sa/4.0
Wurth_Elektronik_Electromechanic_Wire_to: Copyright: Würth Elektronik
